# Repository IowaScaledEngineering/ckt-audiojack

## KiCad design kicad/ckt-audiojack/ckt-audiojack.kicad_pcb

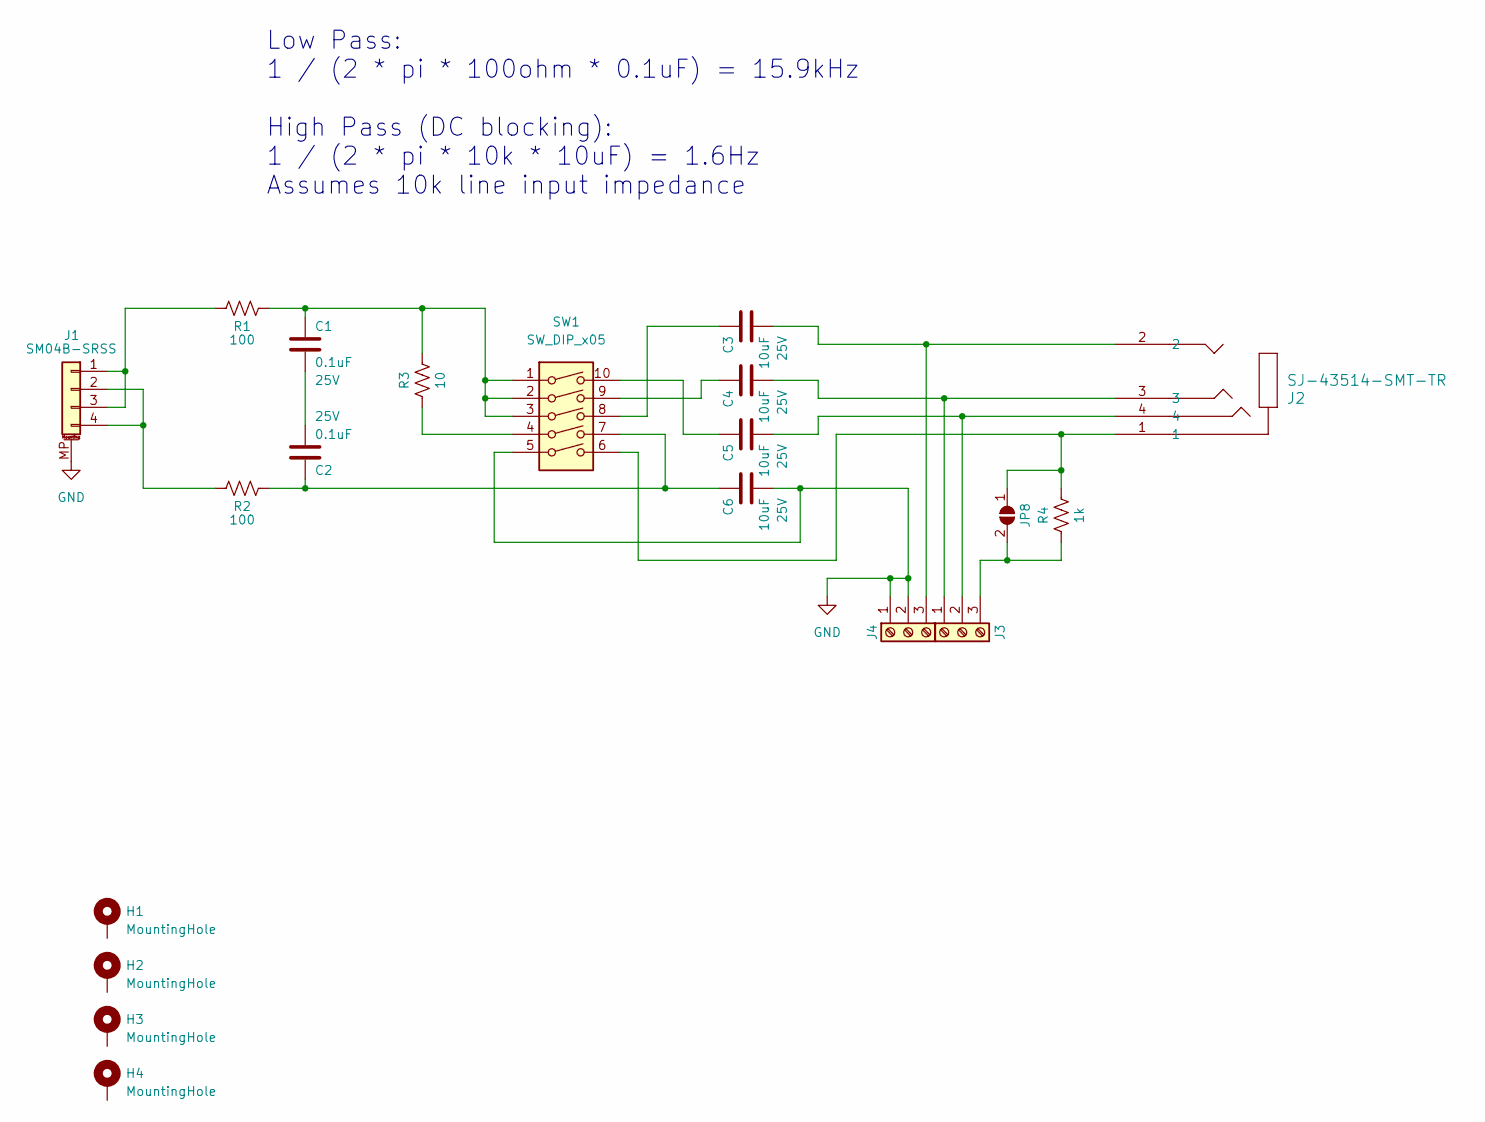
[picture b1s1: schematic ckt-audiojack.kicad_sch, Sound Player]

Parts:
C1, C2: 0.1uF; C_0805_2012Metric; Voltage 25V
C3, C4, C5, C6: 10uF; C_0805_2012Metric; Voltage 25V
H1, H2, H3, H4: MountingHole; MountingHole_3.2mm_M3_Pad
J1: SM04B-SRSS; JST_SH_SM04B-SRSS-TB_1x04-1MP_P1.00mm_Horizontal
J2: SJ-43514-SMT-TR; SJ-43514-SMT_CUD
J3, J4: Screw_Terminal_01x02; TerminalBlock_MetzConnect_Type059_RT06303HBWC_1x03_P3.50mm_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
JP8: SolderJumper_2_Open; SolderJumper-2_P1.3mm_Open_RoundedPad1.0x1.5mm
R1, R2: 100; R_0805_2012Metric
R3: 10; R_0805_2012Metric
R4: 1k; R_0805_2012Metric
SW1: SW_DIP_x05; CST_219SMT

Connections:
GND: C6.2, J1.MP (MountPin), J4.1, J4.2, SW1.5
unnamed: C1.1, R1.1, R3.2, SW1.1, SW1.2, SW1.3
unnamed: C1.2, C2.2
unnamed: C2.1, C6.1, R2.1, SW1.7
unnamed: C3.1, SW1.8
unnamed: C4.1, SW1.9
unnamed: C5.1, SW1.10
unnamed: J1.1, J1.3, R1.2
unnamed: J1.2, J1.4, R2.2
unnamed: C4.2, J2.3, J3.1
unnamed: C5.2, J2.4, J3.2
unnamed: J3.3, JP8.2 (B), R4.1
unnamed: C3.2, J2.2, J4.3
unnamed: J2.1, JP8.1 (A), R4.2, SW1.6
unnamed: R3.1, SW1.4

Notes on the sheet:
Low Pass: 1 / (2 * pi * 100ohm * 0.1uF) = 15.9kHz High Pass (DC blocking): 1 / (2 * pi * 10k * 10uF) = 1.6Hz Assumes 10k line input impedance

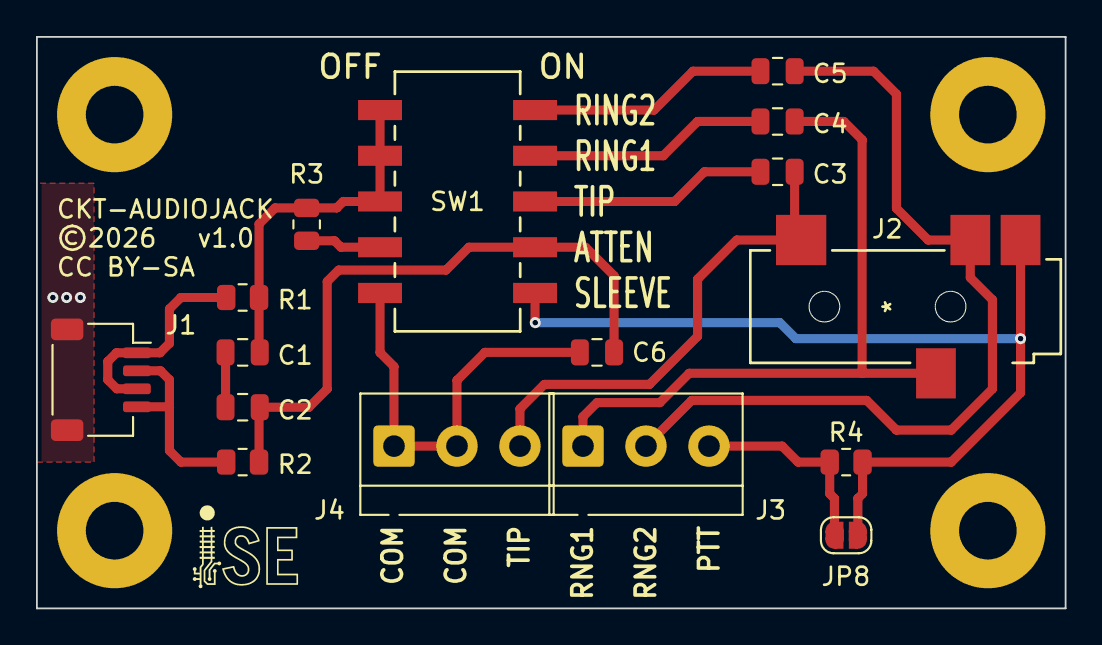
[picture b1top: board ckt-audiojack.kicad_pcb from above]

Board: 2 copper layers, 57.2 x 31.8 mm, 20 parts (0 on the bottom side), 15 nets.

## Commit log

2026-03-18 Updated footprints
2026-03-18 Waived DRC violations
2026-03-19 Small cleanup
2026-03-19 DRC cleanup
2026-03-19 Update to exclude DRC warnings
2026-03-19 PG 1.0

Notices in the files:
kicad/ckt-audiojack/ckt-audiojack.kicad_pcb:
©2026 v1.0
CC BY-SA
